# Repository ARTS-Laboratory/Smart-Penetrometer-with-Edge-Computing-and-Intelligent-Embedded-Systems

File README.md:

# Smart Penetrometer with Edge Computing and Intelligent Embedded Systems (SPECIES) 
### Design and develop UAV-deployable smart sensor nodes in a network with edge computing and solar-charging capabilities for soil classification and fault detection.

## Licensing and Citation

[![CC BY-SA 4.0][cc-by-sa-shield]][cc-by-sa]

This work is licensed under a
[Creative Commons Attribution-ShareAlike 4.0 International License][cc-by-sa].

[cc-by-sa]: http://creativecommons.org/licenses/by-sa/4.0/
[cc-by-sa-image]: https://licensebuttons.net/l/by-sa/4.0/88x31.png
[cc-by-sa-shield]: https://img.shields.io/badge/License-CC%20BY--SA%204.0-lightgrey.svg

Cite as:

@Misc{ARTSLabSmartPenetrometerEdge,  
  author       = {ARTS-Lab},  
  howpublished = {GitHub},  
  title        = {Smart Penetrometer with Edge Computing and Intelligent Embedded Systems},  
  groups       = {ARTS-Lab},  
  url          = {https://github.com/ARTS-Laboratory/Smart-Penetrometers-with-Edge-Computing-and-Intelligent-Embedded-Systems},  
  note = {Accessed: Month dd, yyyy},   
}

<p align="center">
QR code for repo.

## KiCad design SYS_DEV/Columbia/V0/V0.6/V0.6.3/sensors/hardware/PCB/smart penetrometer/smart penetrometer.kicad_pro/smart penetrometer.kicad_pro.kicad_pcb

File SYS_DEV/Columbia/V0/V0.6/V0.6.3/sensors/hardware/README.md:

# Hardware Design
## [CAD](CAD)
### Fusion360 CAD models of sensor node structure

## [PCB](PCB)
### KiCad schematic, PCB, footprints, etc

## [Return to V0.6.0](https://github.com/ARTS-Laboratory/Smart-Penetrometer-with-Edge-Computing-and-Intelligent-Embedded-Systems/blob/main/V0/V0.6/V0.6.0)

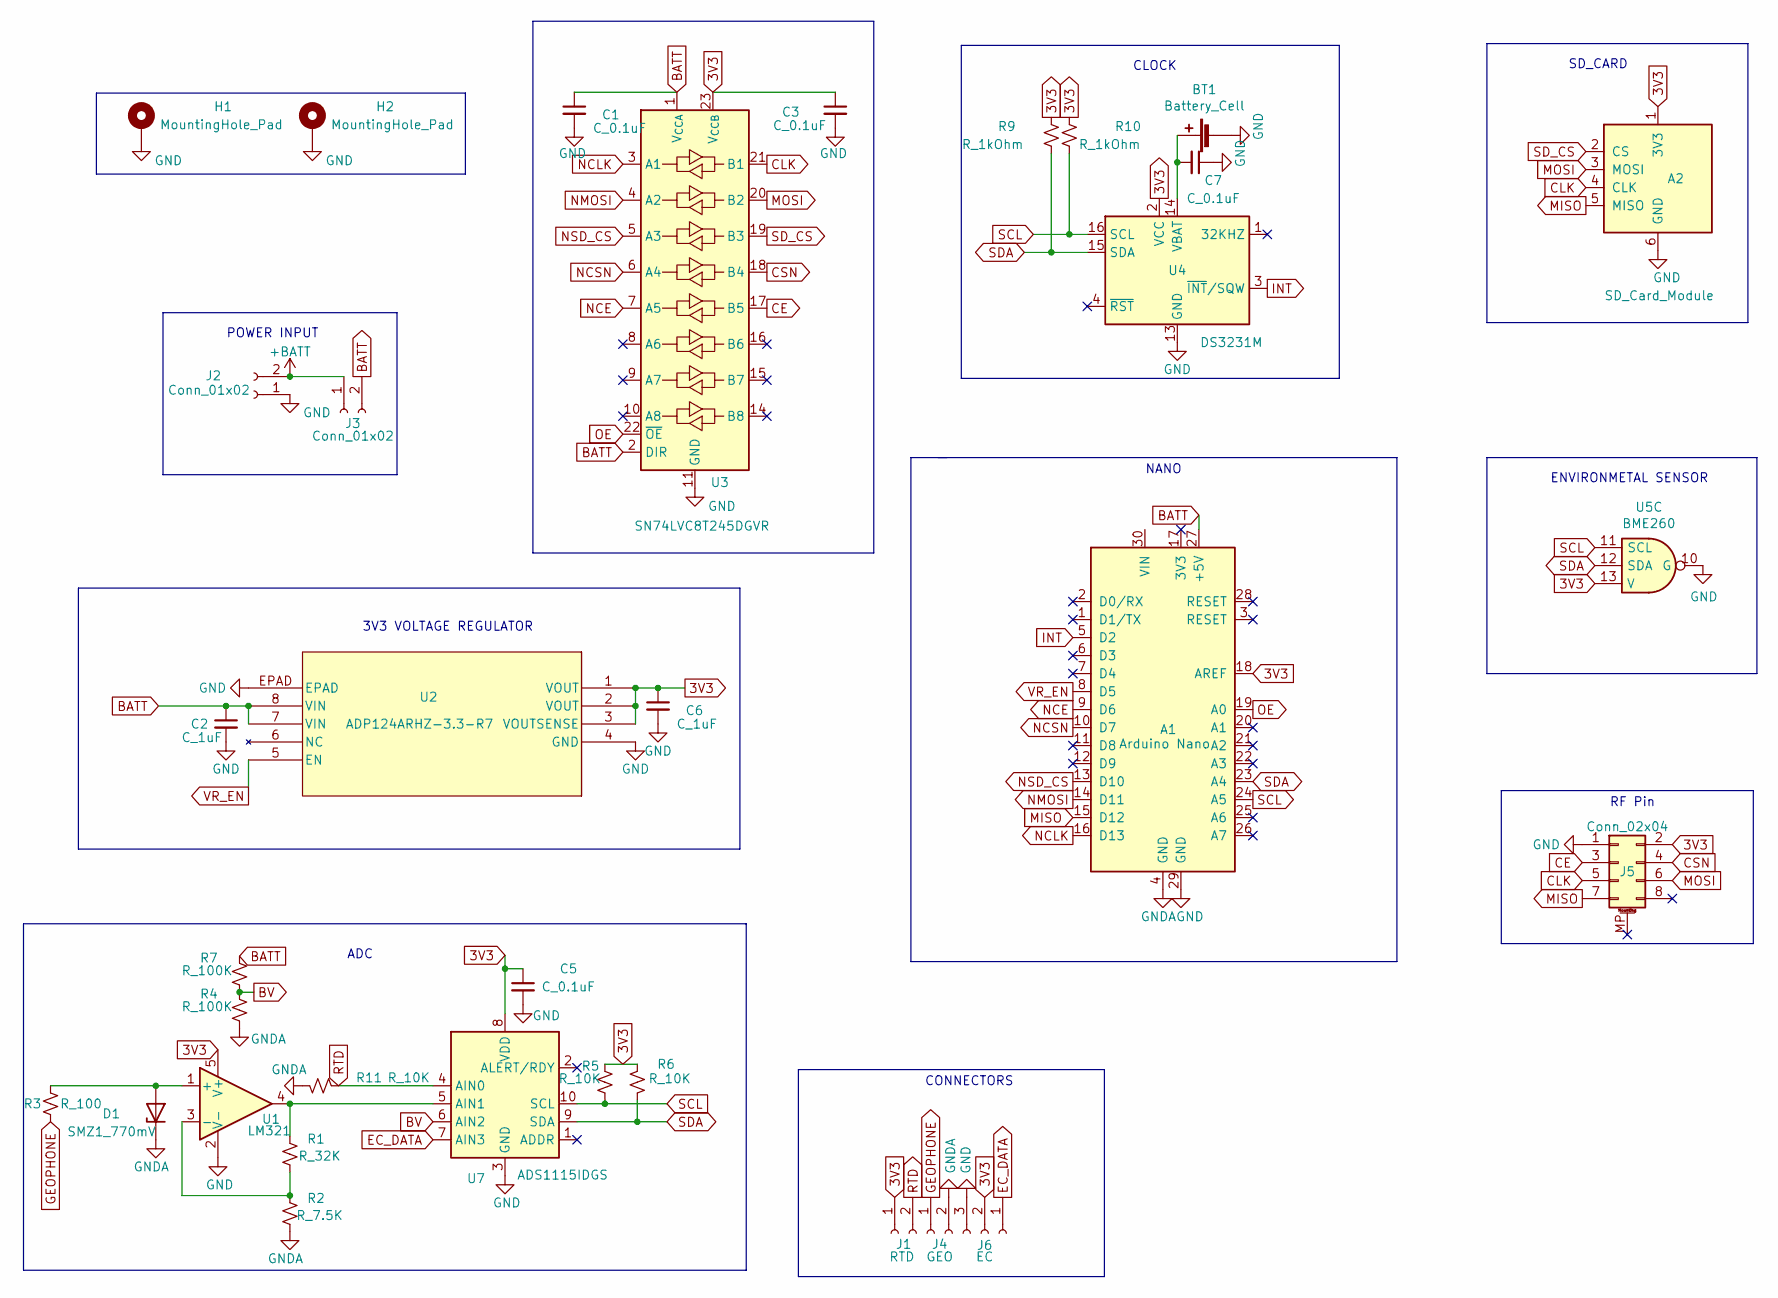
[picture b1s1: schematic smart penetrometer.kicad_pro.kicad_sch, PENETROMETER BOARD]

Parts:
A1: Arduino Nano; Arduino_Nano
A2: SD_Card_Module; SD Module
BT1: Battery_Cell; battery_holder_10mm
C1, C3, C5, C7: C_0.1uF; C_1206_3216Metric
C2, C6: C_1uF; C_1206_3216Metric
D1: SMZ1_770mV; D_MELF
H1, H2: MountingHole_Pad; MountingHole_3.2mm_M3_Pad
J1: RTD; JST_PH_B2B-PH-K_1x02_P2.00mm_Vertical
J2, J3: Conn_01x02; JST_PH_B2B-PH-K_1x02_P2.00mm_Vertical
J4: GEO; JST_PH_B2B-PH-K_1x02_P2.00mm_Vertical
J5: Conn_02x04; PinSocket_2x04_P2.54mm_Vertical
J6: EC; JST_PH_B3B-PH-K_1x03_P2.00mm_Vertical
R1: R_32K; R_1206_3216Metric
R2: R_7.5K; R_1206_3216Metric
R3: R_100; R_1206_3216Metric
R4, R7: R_100K; R_1206_3216Metric
R5, R6, R11: R_10K; R_1206_3216Metric
R9, R10: R_1kOhm; R_1206_3216Metric
U1: LM321; SOT-23-5
U2: ADP124ARHZ-3.3-R7; RH_8_1_ADI
U3: SN74LVC8T245DGVR; SN74LVC8T245DGVR-L
U4: DS3231M; SOIC-16W_7.5x10.3mm_P1.27mm
U5: BME260
U7: ADS1115IDGS; TSSOP-10_3x3mm_P0.5mm

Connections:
3V3: A1.18 (AREF), A2.1 (3V3), C3.1, C5.1, C6.1, J1.1, J5.2, J6.2, R5.1, R6.1, R9.1, R10.1, U1.5 (V+), U2.1 (VOUT), U2.2 (VOUT), U2.3 (VOUTSENSE), U3.23 (V_{CCB}), U3.24 (V_{CCB}), U4.2 (VCC), U5.13, U7.8 (VDD)
+BATT: J2.2, J3.1
BATT: A1.27 (+5V), C1.1, C2.1, J3.2, R7.1, U2.7 (VIN), U2.8 (VIN), U3.1 (V_{CCA}), U3.2 (DIR)
BV: R4.1, R7.2, U7.6 (AIN2)
CE: J5.3, U3.17 (B5)
CLK: A2.4 (CLK), J5.5, U3.21 (B1)
CSN: J5.4, U3.18 (B4)
EC_DATA: J6.1, U7.7 (AIN3)
GEOPHONE: J4.1, R3.1
GND: A1.29 (GND), A2.6 (GND), BT1.2 (-), C1.2, C2.2, C3.2, C5.2, C6.2, C7.1, H1.1, H2.1, J2.1, J5.1, J6.3, U1.2 (V-), U2.4 (GND), U2.EPAD, U3.11 (GND), U3.12 (GND), U3.13 (GND), U4.5 (GND), U4.6 (GND), U4.7 (GND), U4.8 (GND), U4.9 (GND), U4.10 (GND), U4.11 (GND), U4.12 (GND), U4.13 (GND), U5.10, U7.3 (GND)
GNDA: A1.4 (GND), D1.1 (K), J4.2, R2.2, R4.2, R11.2
INT: A1.5 (D2), U4.3 (~INT/SQW)
MISO: A1.15 (D12), A2.5 (MISO), J5.7
MOSI: A2.3 (MOSI), J5.6, U3.20 (B2)
NCE: A1.9 (D6), U3.7 (A5)
NCLK: A1.16 (D13), U3.3 (A1)
NCSN: A1.10 (D7), U3.6 (A4)
NMOSI: A1.14 (D11), U3.4 (A2)
NSD_CS: A1.13 (D10), U3.5 (A3)
unnamed: BT1.1 (+), C7.2, U4.14 (VBAT)
unnamed: D1.2 (A), R3.2, U1.1 (+)
unnamed: R1.2, R2.1, U1.3 (-)
unnamed: R1.1, U1.4, U7.5 (AIN1)
OE: A1.19 (A0), U3.22 (~OE)
RTD: J1.2, R11.1, U7.4 (AIN0)
SCL: A1.24 (A5), R5.2, R10.2, U4.16 (SCL), U5.11, U7.10 (SCL)
SDA: A1.23 (A4), R6.2, R9.2, U4.15 (SDA), U5.12, U7.9 (SDA)
SD_CS: A2.2 (CS), U3.19 (B3)
VR_EN: A1.8 (D5), U2.5 (EN)

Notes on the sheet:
ADC
POWER INPUT
3V3 VOLTAGE REGULATOR
NANO
CLOCK
RF Pin
CONNECTORS
SD_CARD
ENVIRONMETAL SENSOR

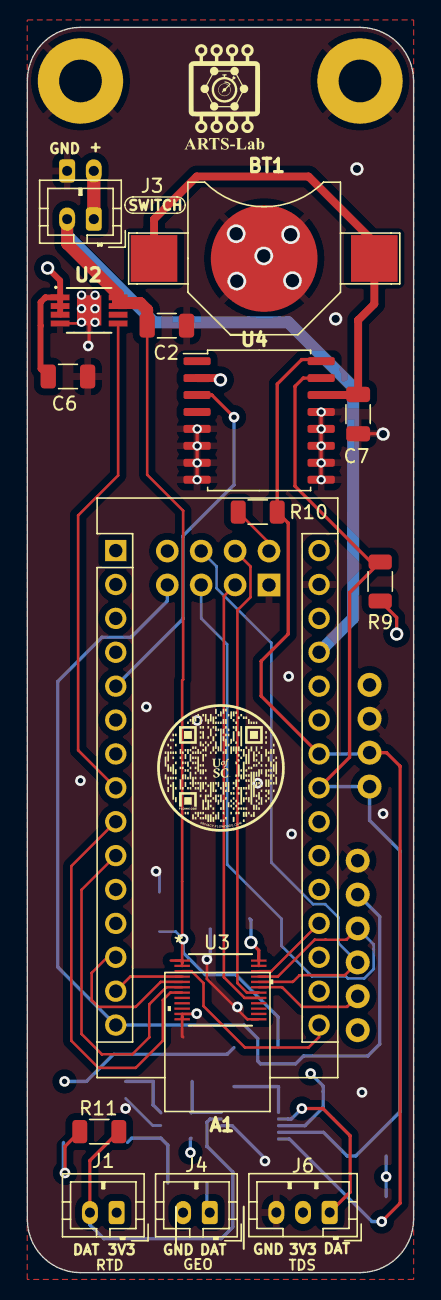
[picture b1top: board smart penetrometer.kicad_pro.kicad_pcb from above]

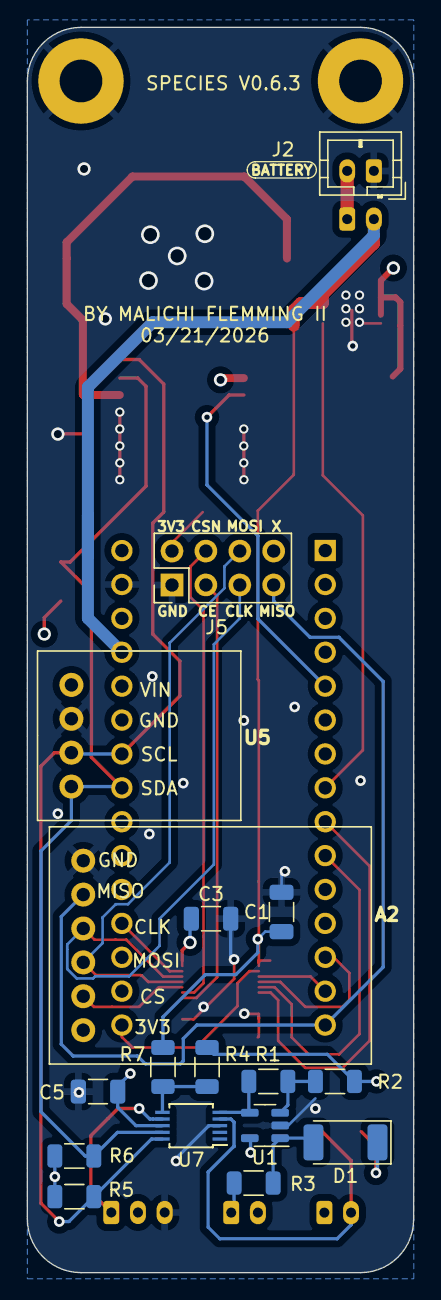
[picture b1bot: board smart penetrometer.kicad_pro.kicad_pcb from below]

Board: 4 copper layers, 29.0 x 93.3 mm, 34 parts (16 on the bottom side), 29 nets.

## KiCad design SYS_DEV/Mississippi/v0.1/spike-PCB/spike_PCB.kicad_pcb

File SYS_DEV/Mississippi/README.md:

# Mississippi

## v0.1
Files related to "spike-only" sensor package version.

### Arduino
`/Arduino/rf24_network.ino` is the code for a sensor spike node. The node's address is declared, data is collected and transmitted to the base station.

A unique address must be assigned to each node in the `this_node` variable in file `Arduino/rf24_network.ino`

`0o00` will be the address of the base station. Each node can be labeled `0o01, 0o02, etc...`

### RaspberryPi
`/RaspberryPi/rf24_network.py` is the code for the base station. The base station's address is established and data is recieved from the children nodes. 

All known nodes must be declared in the `OTHER_NODES` list.
Ex: for 5 nodes connected to base station `OTHER_NODES = [0o1, 0o2, 0o3, 0o4, 0o5]`

*Max of 5 nodes able to connect to nRF24L01+ chip at once.

### Spike PCB
PCB for a sensor spike node.

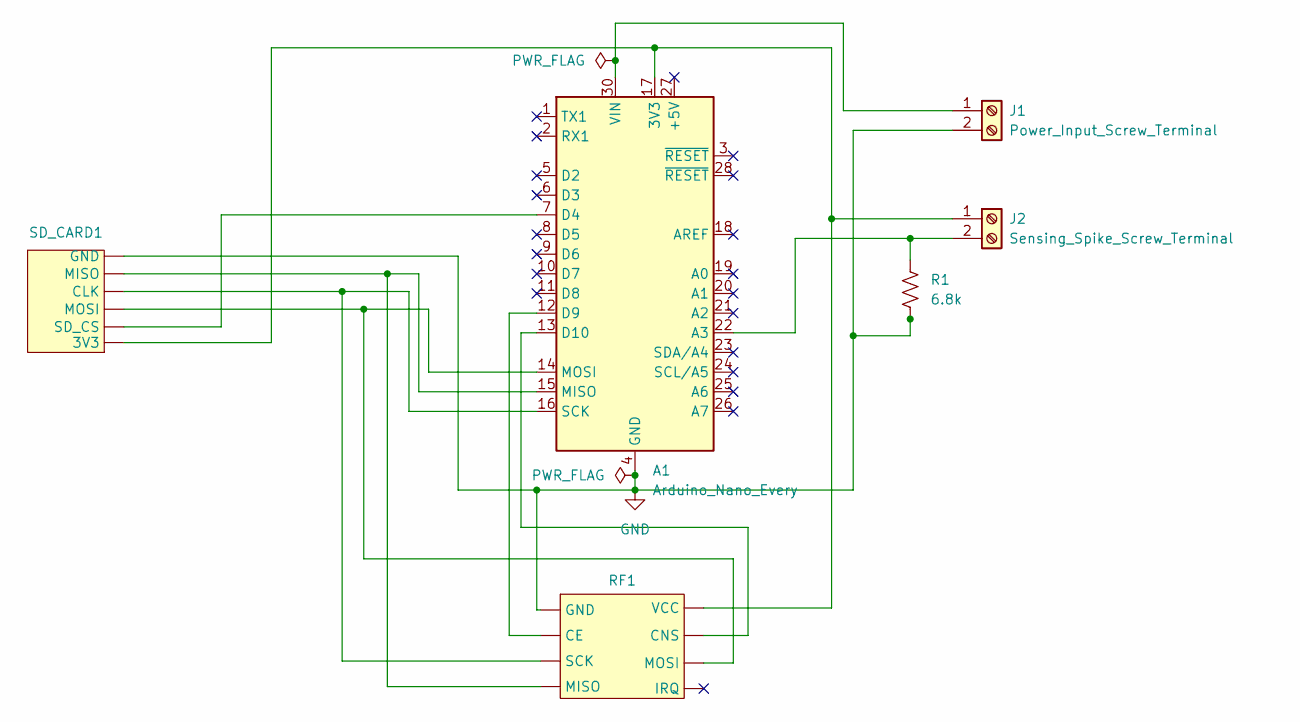
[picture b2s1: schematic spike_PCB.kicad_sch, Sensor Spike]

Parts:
A1: Arduino_Nano_Every; Arduino_Nano
J1: Power_Input_Screw_Terminal; TerminalBlock_Altech_AK300-2_P5.00mm
J2: Sensing_Spike_Screw_Terminal; TerminalBlock_Altech_AK300-2_P5.00mm
R1: 6.8k; R_Axial_DIN0207_L6.3mm_D2.5mm_P7.62mm_Horizontal
RF1: nRF24L01
SD_CARD1: SD_Card_Module

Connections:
GND: A1.4 (GND), A1.29 (GND), J1.2, R1.2, RF1.1 (GND), SD_CARD1.6 (GND)
unnamed: A1.17 (3V3), J2.1, RF1.5 (VCC), SD_CARD1.1 (3V3)
unnamed: A1.22 (A3), J2.2, R1.1
unnamed: A1.7 (D4), SD_CARD1.2 (SD_CS)
unnamed: A1.12 (D9), RF1.2 (CE)
unnamed: A1.13 (D10), RF1.6 (CNS)
unnamed: A1.15 (MISO), RF1.4 (MISO), SD_CARD1.5 (MISO)
unnamed: A1.14 (MOSI), RF1.7 (MOSI), SD_CARD1.3 (MOSI)
unnamed: A1.16 (SCK), RF1.3 (SCK), SD_CARD1.4 (CLK)
unnamed: A1.30 (VIN), J1.1

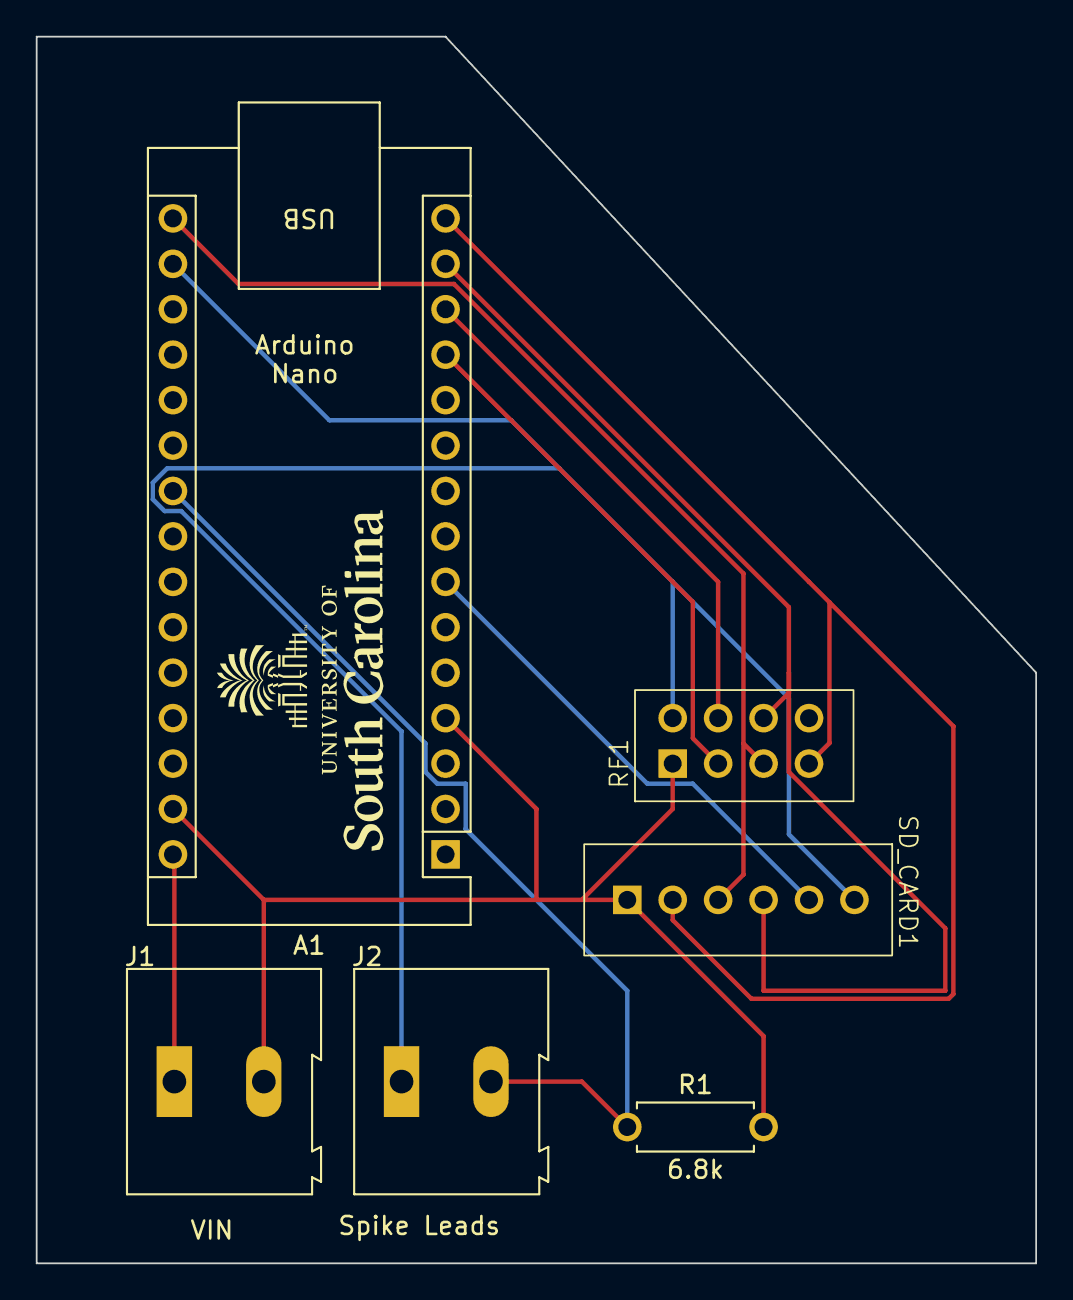
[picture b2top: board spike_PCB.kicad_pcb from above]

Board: 2 copper layers, 55.9 x 68.6 mm, 6 parts (0 on the bottom side), 10 nets.

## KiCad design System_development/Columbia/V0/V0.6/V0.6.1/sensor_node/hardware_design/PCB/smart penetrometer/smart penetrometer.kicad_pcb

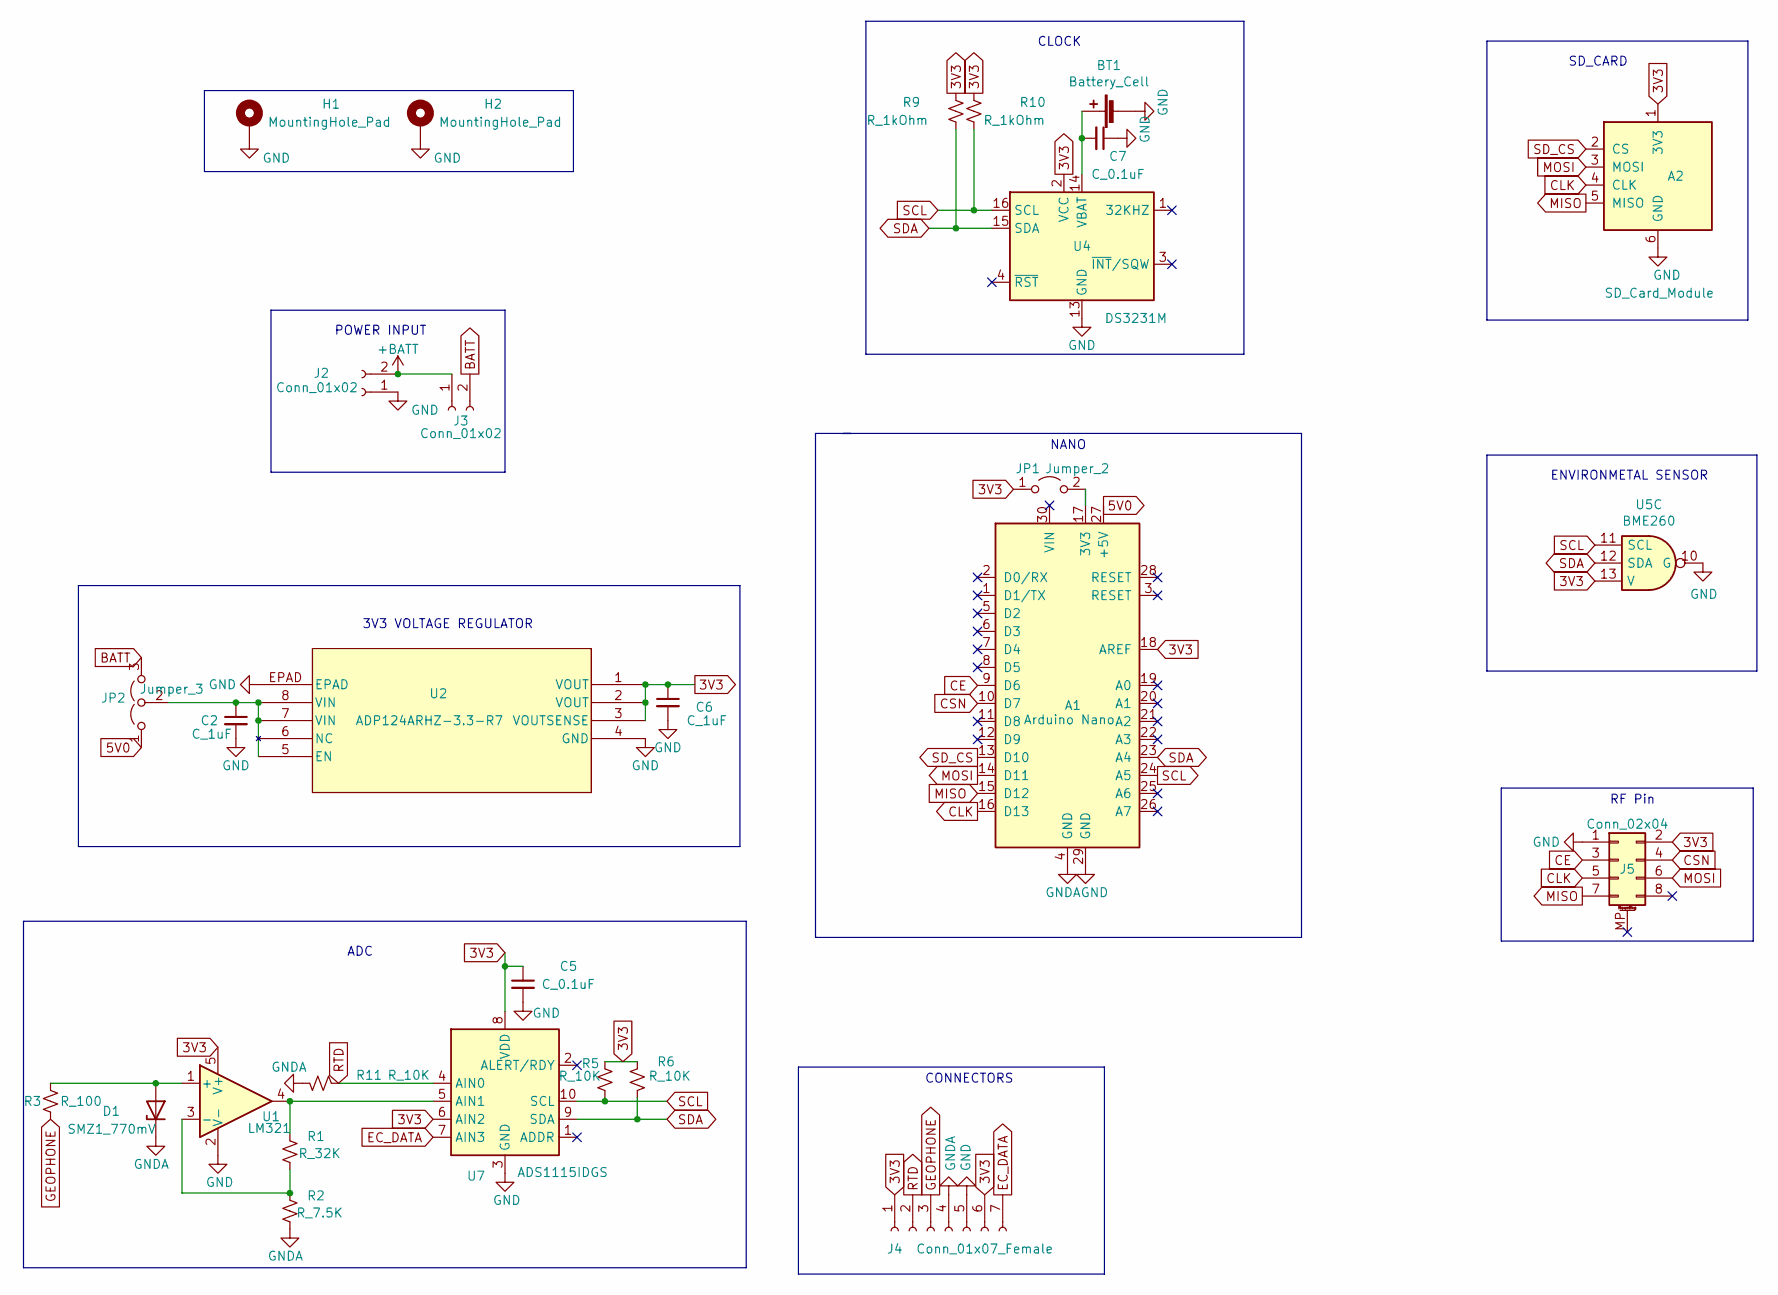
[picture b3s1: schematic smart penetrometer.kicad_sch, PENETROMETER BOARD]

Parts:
A1: Arduino Nano; Arduino_Nano
A2: SD_Card_Module; SD Module
BT1: Battery_Cell; battery_holder_10mm
C2, C6: C_1uF; C_1206_3216Metric
C5, C7: C_0.1uF; C_1206_3216Metric
D1: SMZ1_770mV; D_MELF
H1, H2: MountingHole_Pad; MountingHole_3.2mm_M3_Pad
J2, J3: Conn_01x02; PinSocket_1x02_P2.54mm_Horizontal
J4: Conn_01x07_Female; PinSocket_1x07_P2.54mm_Horizontal
J5: Conn_02x04; PinSocket_2x04_P2.54mm_Vertical
JP1: Jumper_2; PinHeader_1x02_P2.54mm_Vertical
JP2: Jumper_3; PinHeader_1x03_P2.54mm_Vertical
R1: R_32K; R_1206_3216Metric
R2: R_7.5K; R_1206_3216Metric
R3: R_100; R_1206_3216Metric
R5, R6, R11: R_10K; R_1206_3216Metric
R9, R10: R_1kOhm; R_1206_3216Metric
U1: LM321; SOT-23-5
U2: ADP124ARHZ-3.3-R7; RH_8_1_ADI
U4: DS3231M; SOIC-16W_7.5x10.3mm_P1.27mm
U5: BME260
U7: ADS1115IDGS; TSSOP-10_3x3mm_P0.5mm

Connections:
3V3: A1.18 (AREF), A2.1 (3V3), C5.1, C6.1, J4.1, J4.6, J5.2, JP1.1 (A), R5.1, R6.1, R9.1, R10.1, U1.5 (V+), U2.1 (VOUT), U2.2 (VOUT), U2.3 (VOUTSENSE), U4.2 (VCC), U5.13, U7.6 (AIN2), U7.8 (VDD)
5V0: A1.27 (+5V), JP2.1 (A)
+BATT: J2.2, J3.1
BATT: J3.2, JP2.3 (B)
CE: A1.9 (D6), J5.3
CLK: A1.16 (D13), A2.4 (CLK), J5.5
CSN: A1.10 (D7), J5.4
EC_DATA: J4.7, U7.7 (AIN3)
GEOPHONE: J4.3, R3.1
GND: A1.29 (GND), A2.6 (GND), BT1.2 (-), C2.2, C5.2, C6.2, C7.1, H1.1, H2.1, J2.1, J4.5, J5.1, U1.2 (V-), U2.4 (GND), U2.EPAD, U4.5 (GND), U4.6 (GND), U4.7 (GND), U4.8 (GND), U4.9 (GND), U4.10 (GND), U4.11 (GND), U4.12 (GND), U4.13 (GND), U5.10, U7.3 (GND)
GNDA: A1.4 (GND), D1.1 (K), J4.4, R2.2, R11.2
MISO: A1.15 (D12), A2.5 (MISO), J5.7
MOSI: A1.14 (D11), A2.3 (MOSI), J5.6
unnamed: A1.17 (3V3), JP1.2 (B)
unnamed: BT1.1 (+), C7.2, U4.14 (VBAT)
unnamed: D1.2 (A), R3.2, U1.1 (+)
unnamed: C2.1, JP2.2 (C), U2.5 (EN), U2.7 (VIN), U2.8 (VIN)
unnamed: R1.2, R2.1, U1.3 (-)
unnamed: R1.1, U1.4, U7.5 (AIN1)
RTD: J4.2, R11.1, U7.4 (AIN0)
SCL: A1.24 (A5), R5.2, R10.2, U4.16 (SCL), U5.11, U7.10 (SCL)
SDA: A1.23 (A4), R6.2, R9.2, U4.15 (SDA), U5.12, U7.9 (SDA)
SD_CS: A1.13 (D10), A2.2 (CS)

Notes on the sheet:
ADC
POWER INPUT
3V3 VOLTAGE REGULATOR
NANO
CLOCK
RF Pin
CONNECTORS
SD_CARD
ENVIRONMETAL SENSOR

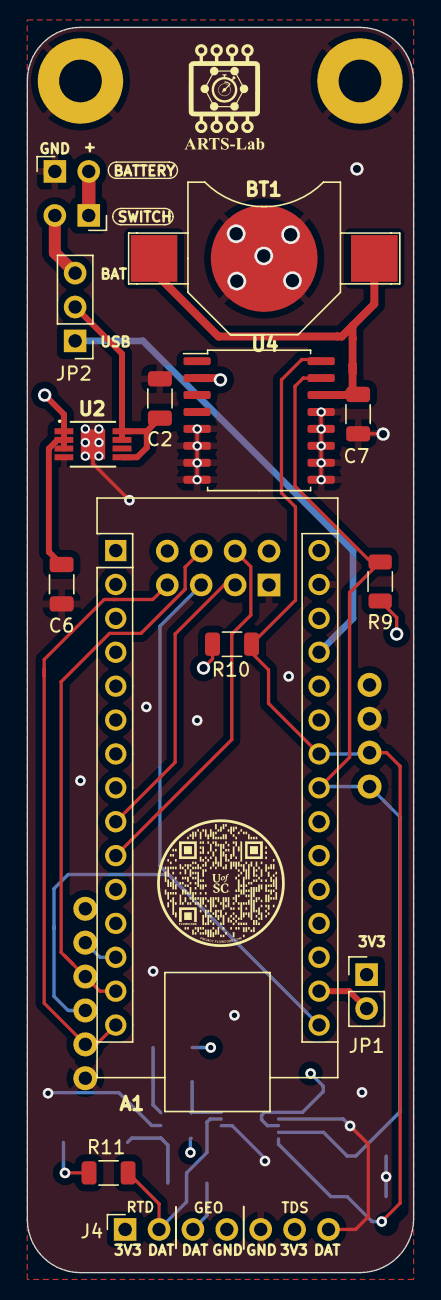
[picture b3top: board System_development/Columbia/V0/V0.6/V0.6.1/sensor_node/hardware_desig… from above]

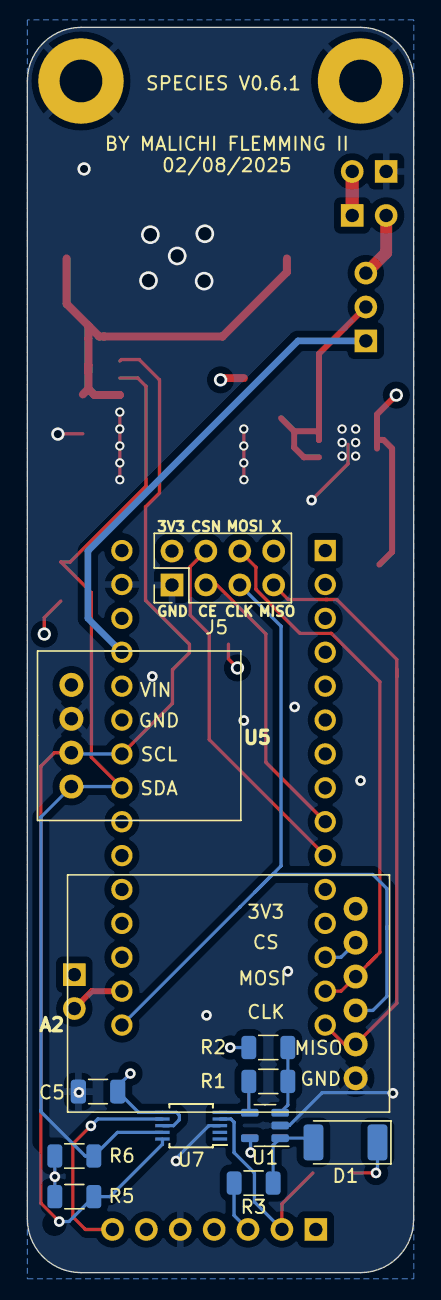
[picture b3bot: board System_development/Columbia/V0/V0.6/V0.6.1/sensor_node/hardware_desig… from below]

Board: 4 copper layers, 29.0 x 93.3 mm, 29 parts (11 on the bottom side), 23 nets.

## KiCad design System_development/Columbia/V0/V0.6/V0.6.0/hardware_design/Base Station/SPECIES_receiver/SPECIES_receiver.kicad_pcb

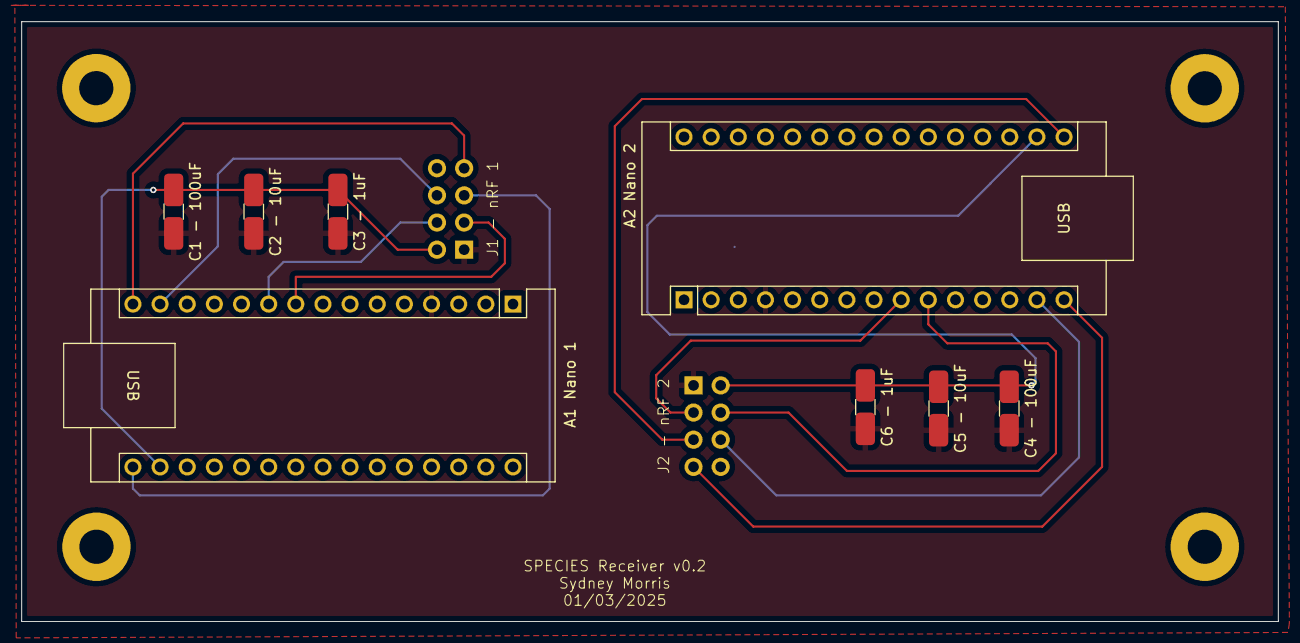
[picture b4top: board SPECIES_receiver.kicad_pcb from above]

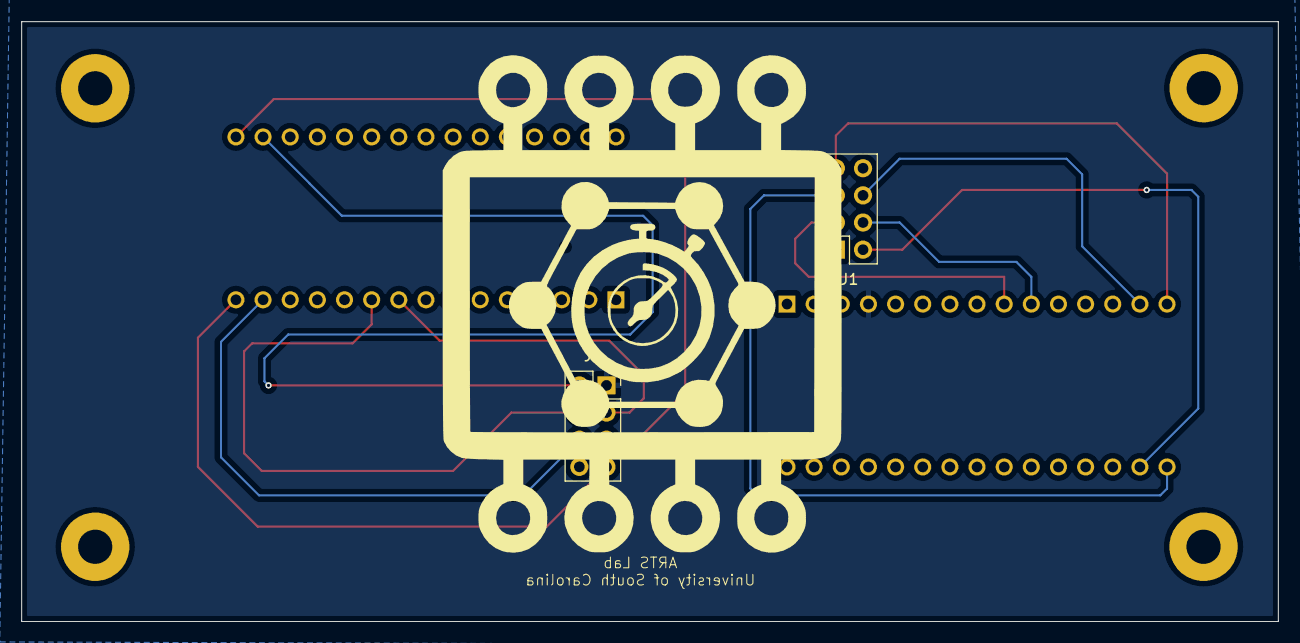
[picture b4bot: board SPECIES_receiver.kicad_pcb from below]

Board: 2 copper layers, 117.6 x 56.1 mm, 10 parts (2 on the bottom side), 8 nets.

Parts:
A1: Nano 1; Arduino_Nano
A2: Nano 2; Arduino_Nano
C1 - 100uF, C2 - 10uF, C3 - 1uF, C4 - 100uF, C5 - 10uF, C6 - 1uF: C_Small; C_1206_3216Metric
J1, J2: Conn_02x04_Odd_Even_MountingPin; PinSocket_2x04_P2.54mm_Vertical

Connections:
3V3: A1.17 (3V3), A2.17 (3V3), C1 - 100uF.1, C2 - 10uF.1, C3 - 1uF.1, C4 - 100uF.1, C5 - 10uF.1, C6 - 1uF.1, J1.2, J2.2
CE: A1.9 (D6), A2.9 (D6), J1.3, J2.3
CLK: A1.16 (D13), A2.16 (D13), J1.5, J2.5
CSN: A1.10 (D7), A2.10 (D7), J1.4, J2.4
GND: A1.4 (GND), A2.4 (GND), C1 - 100uF.2, C2 - 10uF.2, C3 - 1uF.2, C4 - 100uF.2, C5 - 10uF.2, C6 - 1uF.2, J1.1, J2.1
MISO: A1.15 (D12), A2.15 (D12), J1.7, J2.7
MOSI: A1.14 (D11), A2.14 (D11), J1.6, J2.6
unnamed: A2.27 (+5V), A2.30 (VIN)

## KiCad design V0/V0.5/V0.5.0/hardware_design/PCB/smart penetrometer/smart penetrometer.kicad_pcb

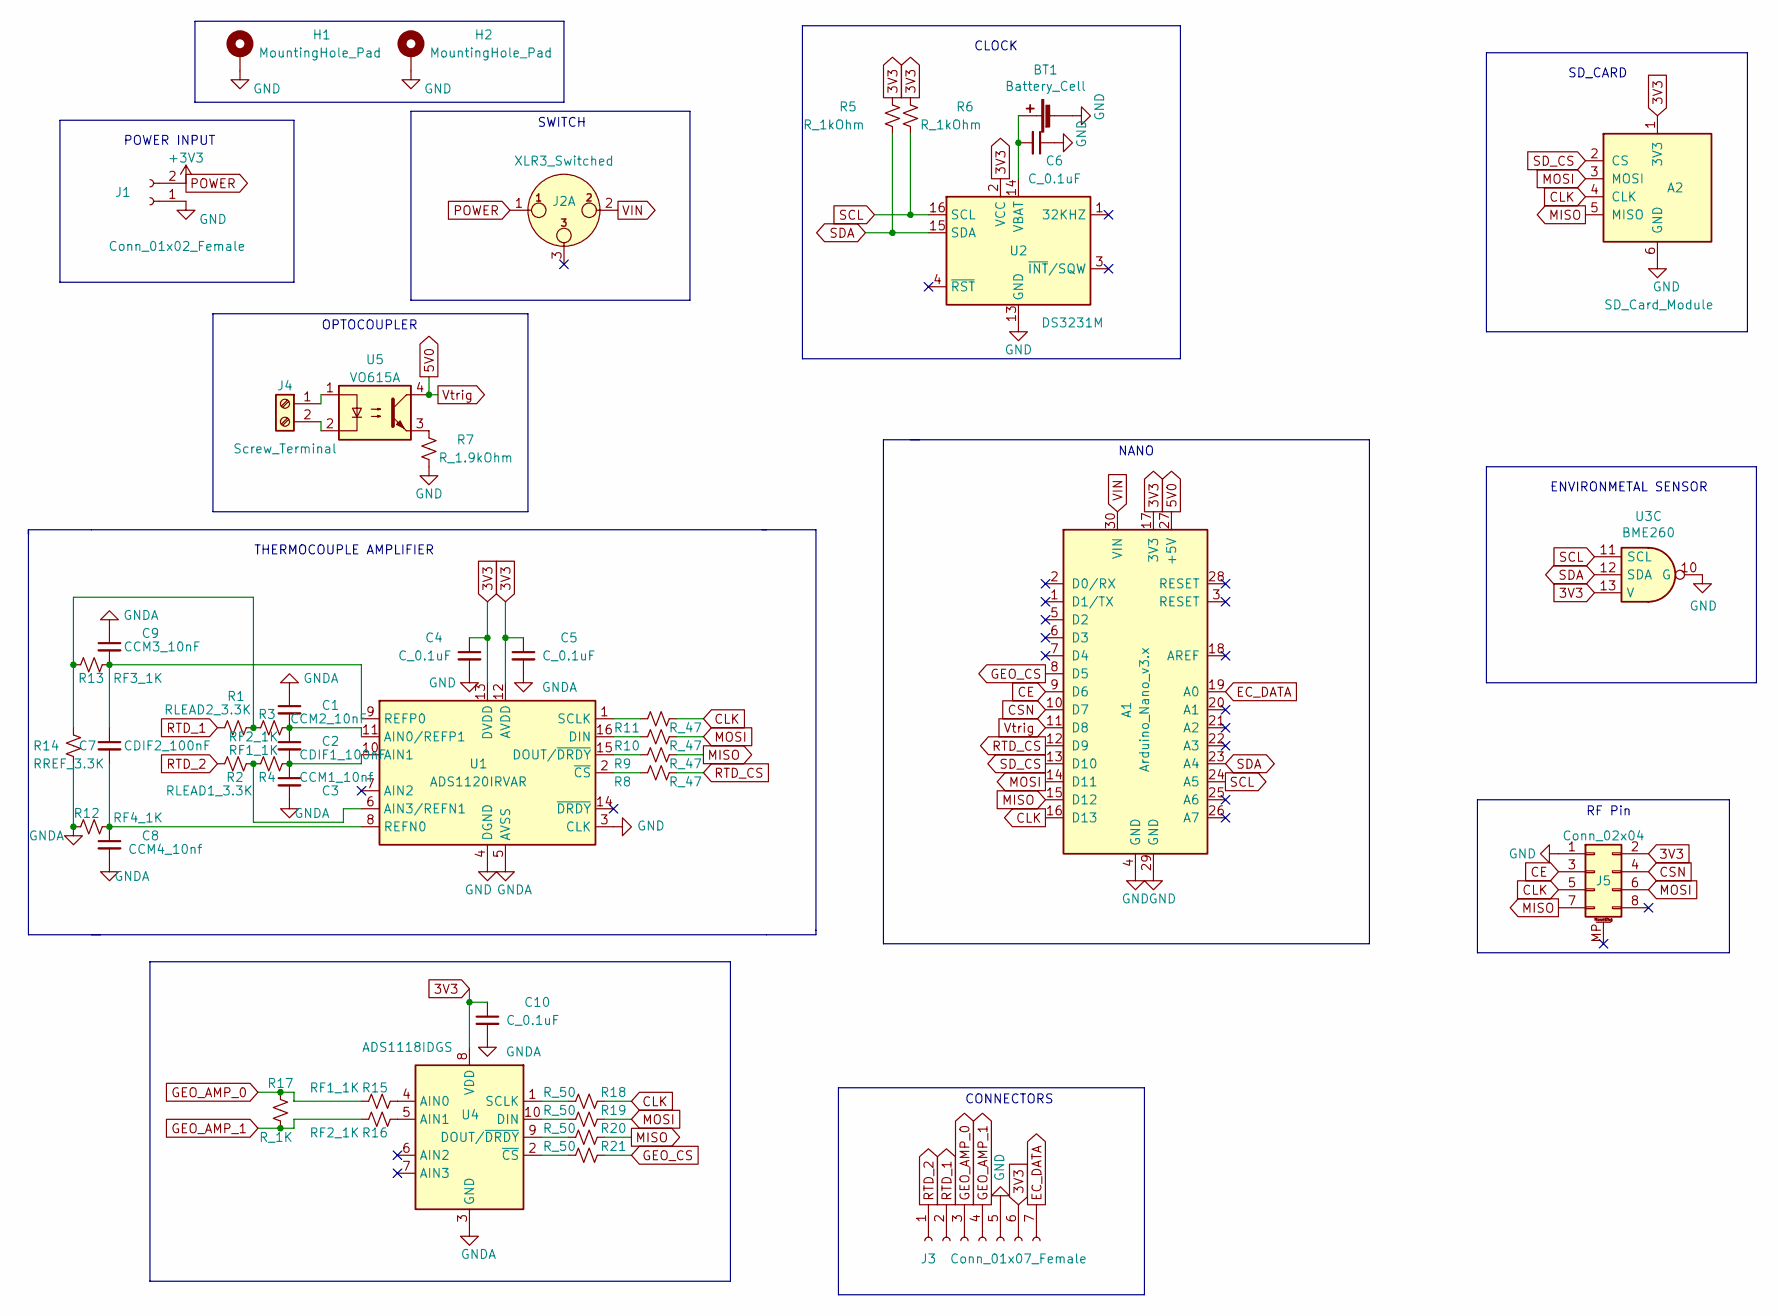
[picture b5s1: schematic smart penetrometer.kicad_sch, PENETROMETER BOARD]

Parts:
A1: Arduino_Nano_v3.x; Arduino_Nano
A2: SD_Card_Module; SD Module
BT1: Battery_Cell; battery_holder_10mm
C1: CCM2_10nF; C_1206_3216Metric
C2: CDIF1_100nF; C_1206_3216Metric
C3: CCM1_10nf; C_1206_3216Metric
C4, C5, C6, C10: C_0.1uF; C_1206_3216Metric
C7: CDIF2_100nF; C_1206_3216Metric
C8: CCM4_10nf; C_1206_3216Metric
C9: CCM3_10nF; C_1206_3216Metric
H1, H2: MountingHole_Pad; MountingHole_3.2mm_M3_Pad
J1: Conn_01x02_Female; PinSocket_1x02_P2.54mm_Horizontal
J2: XLR3_Switched; grounded_switch
J3: Conn_01x07_Female; PinSocket_1x07_P2.54mm_Horizontal
J4: Screw_Terminal; TerminalBlock_bornier-2_P5.08mm
J5: Conn_02x04; PinSocket_2x04_P2.54mm_Vertical
R1: RLEAD2_3.3K; R_1206_3216Metric
R2: RLEAD1_3.3K; R_1206_3216Metric
R3, R16: RF2_1K; R_1206_3216Metric
R4, R15: RF1_1K; R_1206_3216Metric
R5, R6: R_1kOhm; R_1206_3216Metric
R7: R_1.9kOhm; R_1206_3216Metric
R8, R9, R10, R11: R_47; R_1206_3216Metric
R12: RF4_1K; R_1206_3216Metric
R13: RF3_1K; R_1206_3216Metric
R14: RREF_3.3K; R_1206_3216Metric
R17: R_1K; R_1206_3216Metric
R18, R19, R20, R21: R_50; R_1206_3216Metric
U1: ADS1120IRVAR; ADS1120IPW 16TSSOP
U2: DS3231M; SOIC-16W_7.5x10.3mm_P1.27mm
U3: BME260; TDS_module
U4: ADS1118IDGS; ADS1118_10VSSOP
U5: VO615A; Vishay_VOS615A

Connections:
3V3: A1.17 (3V3), A2.1 (3V3), C4.1, C5.1, C10.1, J3.6, J5.2, R5.1, R6.1, U1.12 (AVDD), U1.13 (DVDD), U2.2 (VCC), U3.13, U4.8 (VDD)
5V0: A1.11 (D8), A1.27 (+5V), U5.4
CE: A1.9 (D6), J5.3
CLK: A1.16 (D13), A2.4 (CLK), J5.5, R11.1, R18.1
CSN: A1.10 (D7), J5.4
EC_DATA: A1.19 (A0), J3.7
GEO_AMP_0: J3.3, R15.2, R17.1
GEO_AMP_1: J3.4, R16.2, R17.2
GEO_CS: A1.8 (D5), R21.1
MISO: A1.15 (D12), A2.5 (MISO), J5.7, R9.1, R20.1
MOSI: A1.14 (D11), A2.3 (MOSI), J5.6, R10.1, R19.1
unnamed: BT1.1 (+), C6.2, U2.14 (VBAT)
unnamed: J4.1, U5.1
unnamed: J4.2, U5.2
unnamed: R1.1, R3.2, R13.1, R14.2
unnamed: R7.1, U5.3
unnamed: C1.2, C2.1, R3.1, U1.11 (AIN0/REFP1)
unnamed: C2.2, C3.1, R4.1, U1.10 (AIN1)
unnamed: R2.2, R4.2, U1.6 (AIN3/REFN1)
unnamed: R10.2, U1.16 (DIN)
unnamed: R9.2, U1.15 (DOUT/~DRDY)
unnamed: C7.2, C8.1, R12.2, U1.8 (REFN0)
unnamed: C7.1, C9.2, R13.2, U1.9 (REFP0)
unnamed: R11.2, U1.1 (SCLK)
unnamed: R8.2, U1.2 (~CS)
unnamed: R15.1, U4.4 (AIN0)
unnamed: R16.1, U4.5 (AIN1)
unnamed: R19.2, U4.10 (DIN)
unnamed: R20.2, U4.9 (DOUT/~DRDY)
unnamed: R18.2, U4.1 (SCLK)
unnamed: R21.2, U4.2 (~CS)
POWER: J1.2, J2.1
RTD_1: J3.2, R1.2
RTD_2: J3.1, R2.1
RTD_CS: A1.12 (D9), R8.1
SCL: A1.24 (A5), R6.2, U2.16 (SCL), U3.11
SDA: A1.23 (A4), R5.2, U2.15 (SDA), U3.12
SD_CS: A1.13 (D10), A2.2 (CS)
VIN: A1.30 (VIN), J2.2

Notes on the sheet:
THERMOCOUPLE AMPLIFIER
POWER INPUT
NANO
SWITCH
CLOCK
RF Pin
CONNECTORS
SD_CARD
ENVIRONMETAL SENSOR
OPTOCOUPLER

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
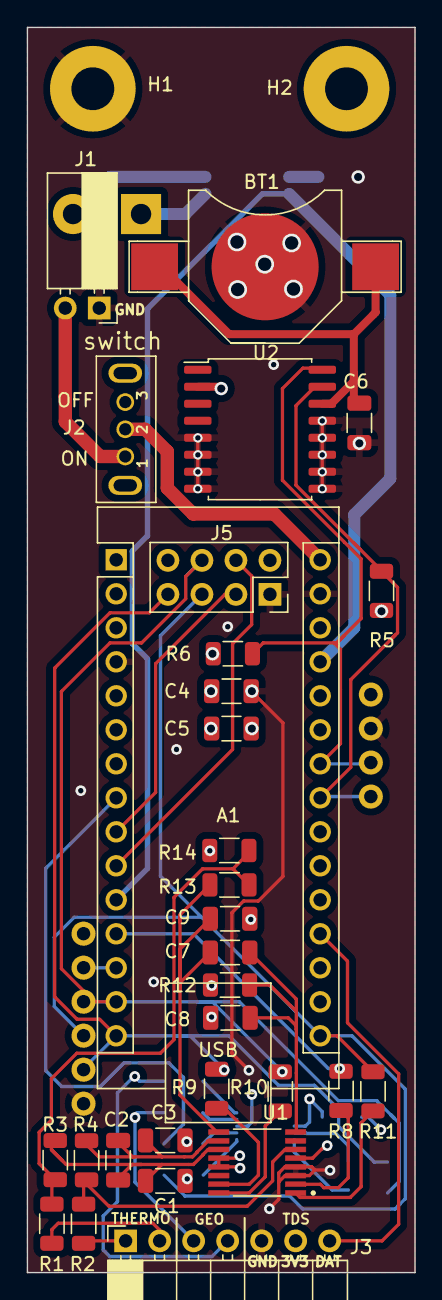
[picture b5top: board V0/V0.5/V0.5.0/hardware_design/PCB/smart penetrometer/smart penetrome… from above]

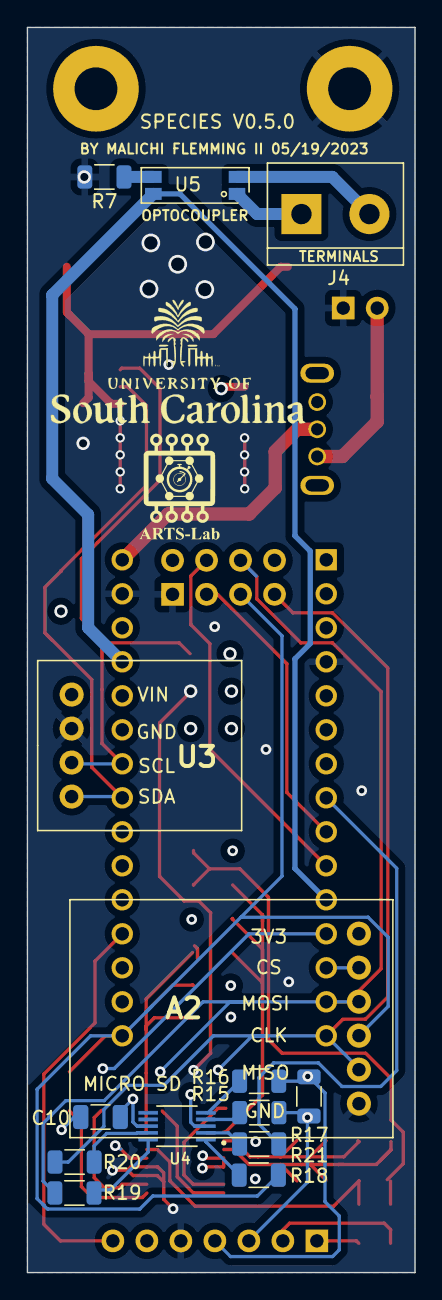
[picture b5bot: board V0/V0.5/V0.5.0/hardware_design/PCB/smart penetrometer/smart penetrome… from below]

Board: 4 copper layers, 29.0 x 93.0 mm, 46 parts (14 on the bottom side), 41 nets.

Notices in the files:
parts and their libraries:
Copyright 2021 Accelerated Designs. All rights reserved.
